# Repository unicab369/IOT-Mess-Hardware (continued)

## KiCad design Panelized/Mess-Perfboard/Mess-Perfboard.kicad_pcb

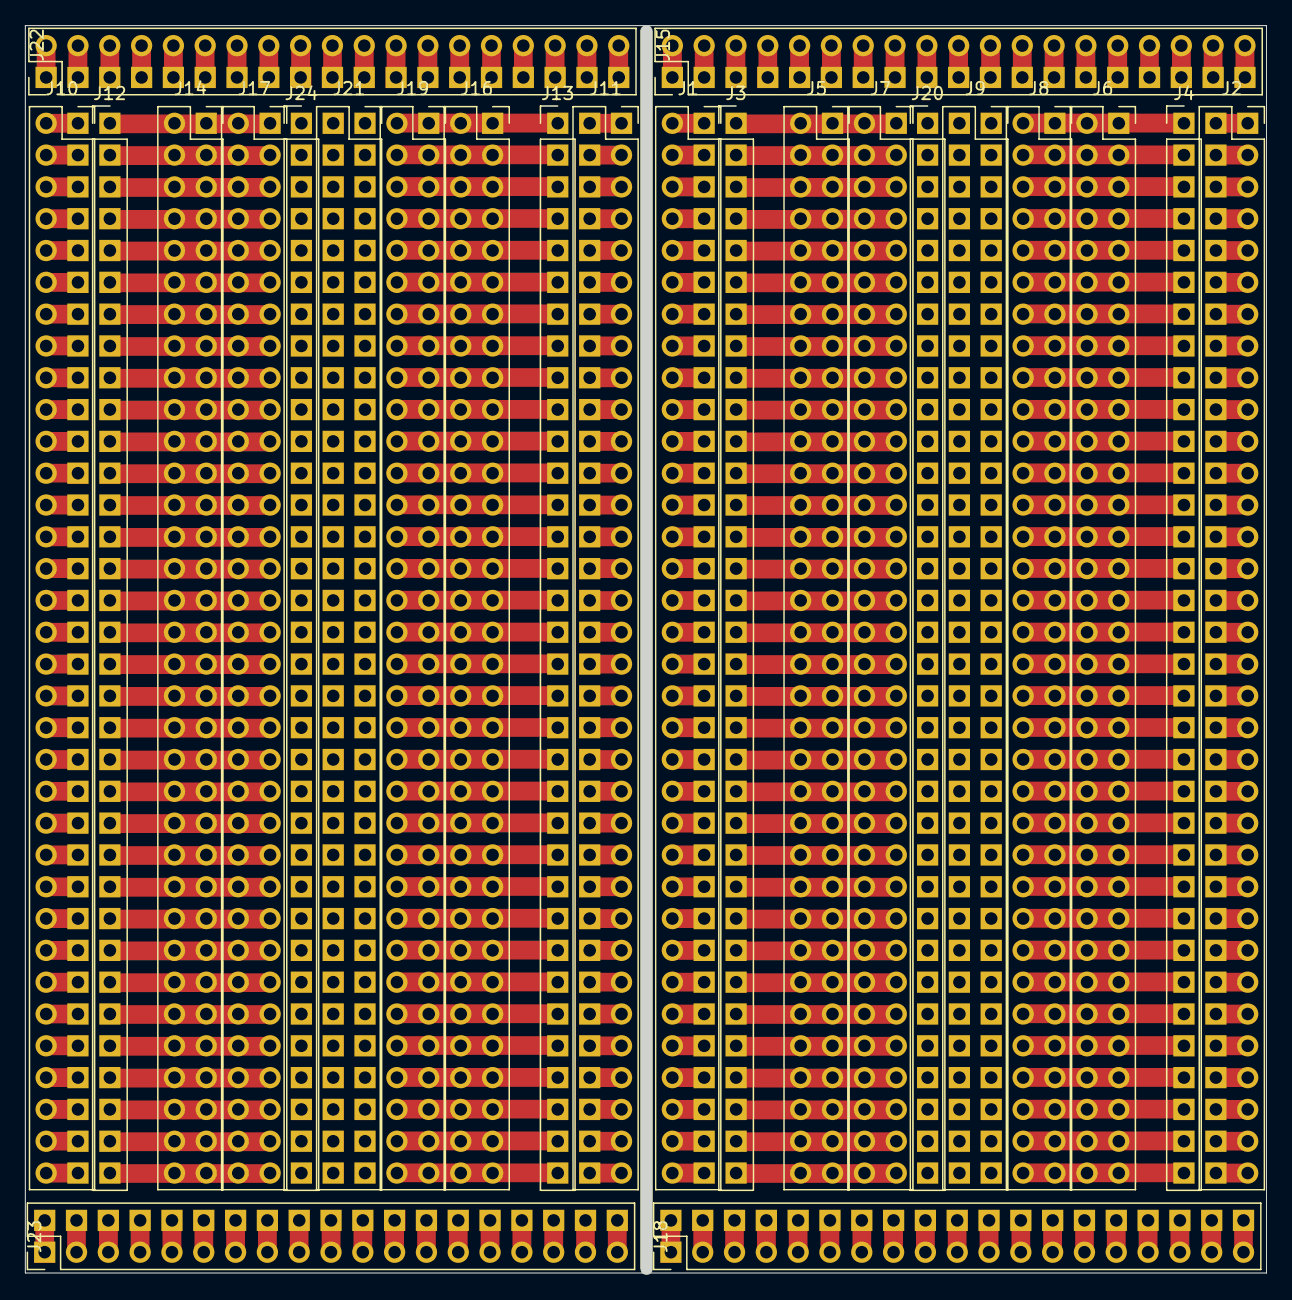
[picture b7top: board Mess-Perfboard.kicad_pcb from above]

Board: 2 copper layers, 99.1 x 99.6 mm, 24 parts (0 on the bottom side), 174 nets.

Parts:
J1, J2, J5, J6, J7, J8, J9, J10, J11, J14, J16, J17, J19, J21: Conn_02x34_Odd_Even; PinSocket_2x34_P2.54mm_Vertical
J3, J4, J12, J13, J20, J24: Conn_01x34_Pin; PinHeader_1x34_P2.54mm_Vertical
J15, J18, J22, J23: Conn_02x19_Odd_Even; PinHeader_2x19_P2.54mm_Vertical

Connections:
/A1: J1.1, J1.2, J10.1, J10.2
/A2: J1.3, J1.4, J10.3, J10.4
/A3: J1.5, J1.6, J10.5, J10.6
/A4: J1.7, J1.8, J10.7, J10.8
/A5: J1.9, J1.10, J10.9, J10.10
/A6: J1.11, J1.12, J10.11, J10.12
/A7: J1.13, J1.14, J10.13, J10.14
/A8: J1.15, J1.16, J10.15, J10.16
/A9: J1.17, J1.18, J10.17, J10.18
/A10: J1.19, J1.20, J10.19, J10.20
/A11: J1.21, J1.22, J10.21, J10.22
/A12: J1.23, J1.24, J10.23, J10.24
/A13: J1.25, J1.26, J10.25, J10.26
/A14: J1.27, J1.28, J10.27, J10.28
/A15: J1.29, J1.30, J10.29, J10.30
/A16: J1.31, J1.32, J10.31, J10.32
/A17: J1.33, J1.34, J10.33, J10.34
/A18: J1.35, J1.36, J10.35, J10.36
/A19: J1.37, J1.38, J10.37, J10.38
/A20: J1.39, J1.40, J10.39, J10.40
/A21: J1.41, J1.42, J10.41, J10.42
/A22: J1.43, J1.44, J10.43, J10.44
/A23: J1.45, J1.46, J10.45, J10.46
/A24: J1.47, J1.48, J10.47, J10.48
/A25: J1.49, J1.50, J10.49, J10.50
/A26: J1.51, J1.52, J10.51, J10.52
/A27: J1.53, J1.54, J10.53, J10.54
/A28: J1.55, J1.56, J10.55, J10.56
/A29: J1.57, J1.58, J10.57, J10.58
/A30: J1.59, J1.60, J10.59, J10.60
/A31: J1.61, J1.62, J10.61, J10.62
/A32: J1.63, J1.64, J10.63, J10.64
/A33: J1.65, J1.66, J10.65, J10.66
/A34: J1.67, J1.68, J10.67, J10.68
/B1: J3.1, J5.1, J5.2, J7.1, J7.2, J12.1, J14.1, J14.2, J17.1, J17.2
/B2: J3.2, J5.3, J5.4, J7.3, J7.4, J12.2, J14.3, J14.4, J17.3, J17.4
/B3: J3.3, J5.5, J5.6, J7.5, J7.6, J12.3, J14.5, J14.6, J17.5, J17.6
/B4: J3.4, J5.7, J5.8, J7.7, J7.8, J12.4, J14.7, J14.8, J17.7, J17.8
/B5: J3.5, J5.9, J5.10, J7.9, J7.10, J12.5, J14.9, J14.10, J17.9, J17.10
/B6: J3.6, J5.11, J5.12, J7.11, J7.12, J12.6, J14.11, J14.12, J17.11, J17.12
/B7: J3.7, J5.13, J5.14, J7.13, J7.14, J12.7, J14.13, J14.14, J17.13, J17.14
/B8: J3.8, J5.15, J5.16, J7.15, J7.16, J12.8, J14.15, J14.16, J17.15, J17.16
/B9: J3.9, J5.17, J5.18, J7.17, J7.18, J12.9, J14.17, J14.18, J17.17, J17.18
/B10: J3.10, J5.19, J5.20, J7.19, J7.20, J12.10, J14.19, J14.20, J17.19, J17.20
/B11: J3.11, J5.21, J5.22, J7.21, J7.22, J12.11, J14.21, J14.22, J17.21, J17.22
/B12: J3.12, J5.23, J5.24, J7.23, J7.24, J12.12, J14.23, J14.24, J17.23, J17.24
/B13: J3.13, J5.25, J5.26, J7.25, J7.26, J12.13, J14.25, J14.26, J17.25, J17.26
/B14: J3.14, J5.27, J5.28, J7.27, J7.28, J12.14, J14.27, J14.28, J17.27, J17.28
/B15: J3.15, J5.29, J5.30, J7.29, J7.30, J12.15, J14.29, J14.30, J17.29, J17.30
/B16: J3.16, J5.31, J5.32, J7.31, J7.32, J12.16, J14.31, J14.32, J17.31, J17.32
/B17: J3.17, J5.33, J5.34, J7.33, J7.34, J12.17, J14.33, J14.34, J17.33, J17.34
/B18: J3.18, J5.35, J5.36, J7.35, J7.36, J12.18, J14.35, J14.36, J17.35, J17.36
/B19: J3.19, J5.37, J5.38, J7.37, J7.38, J12.19, J14.37, J14.38, J17.37, J17.38
/B20: J3.20, J5.39, J5.40, J7.39, J7.40, J12.20, J14.39, J14.40, J17.39, J17.40
/B21: J3.21, J5.41, J5.42, J7.41, J7.42, J12.21, J14.41, J14.42, J17.41, J17.42
/B22: J3.22, J5.43, J5.44, J7.43, J7.44, J12.22, J14.43, J14.44, J17.43, J17.44
/B23: J3.23, J5.45, J5.46, J7.45, J7.46, J12.23, J14.45, J14.46, J17.45, J17.46
/B24: J3.24, J5.47, J5.48, J7.47, J7.48, J12.24, J14.47, J14.48, J17.47, J17.48
/B25: J3.25, J5.49, J5.50, J7.49, J7.50, J12.25, J14.49, J14.50, J17.49, J17.50
/B26: J3.26, J5.51, J5.52, J7.51, J7.52, J12.26, J14.51, J14.52, J17.51, J17.52
/B27: J3.27, J5.53, J5.54, J7.53, J7.54, J12.27, J14.53, J14.54, J17.53, J17.54
/B28: J3.28, J5.55, J5.56, J7.55, J7.56, J12.28, J14.55, J14.56, J17.55, J17.56
/B29: J3.29, J5.57, J5.58, J7.57, J7.58, J12.29, J14.57, J14.58, J17.57, J17.58
/B30: J3.30, J5.59, J5.60, J7.59, J7.60, J12.30, J14.59, J14.60, J17.59, J17.60
/B31: J3.31, J5.61, J5.62, J7.61, J7.62, J12.31, J14.61, J14.62, J17.61, J17.62
/B32: J3.32, J5.63, J5.64, J7.63, J7.64, J12.32, J14.63, J14.64, J17.63, J17.64
/B33: J3.33, J5.65, J5.66, J7.65, J7.66, J12.33, J14.65, J14.66, J17.65, J17.66
/B34: J3.34, J5.67, J5.68, J7.67, J7.68, J12.34, J14.67, J14.68, J17.67, J17.68
/C1: J2.1, J2.2, J11.1, J11.2
/C2: J2.3, J2.4, J11.3, J11.4
/C3: J2.5, J2.6, J11.5, J11.6
/C4: J2.7, J2.8, J11.7, J11.8
/C5: J2.9, J2.10, J11.9, J11.10
/C6: J2.11, J2.12, J11.11, J11.12
/C7: J2.13, J2.14, J11.13, J11.14
/C8: J2.15, J2.16, J11.15, J11.16
/C9: J2.17, J2.18, J11.17, J11.18
/C10: J2.19, J2.20, J11.19, J11.20
/C11: J2.21, J2.22, J11.21, J11.22
/C12: J2.23, J2.24, J11.23, J11.24
/C13: J2.25, J2.26, J11.25, J11.26
/C14: J2.27, J2.28, J11.27, J11.28
/C15: J2.29, J2.30, J11.29, J11.30
/C16: J2.31, J2.32, J11.31, J11.32
/C17: J2.33, J2.34, J11.33, J11.34
/C18: J2.35, J2.36, J11.35, J11.36
/C19: J2.37, J2.38, J11.37, J11.38
/C20: J2.39, J2.40, J11.39, J11.40
/C21: J2.41, J2.42, J11.41, J11.42
/C22: J2.43, J2.44, J11.43, J11.44
/C23: J2.45, J2.46, J11.45, J11.46
/C24: J2.47, J2.48, J11.47, J11.48
/C25: J2.49, J2.50, J11.49, J11.50
/C26: J2.51, J2.52, J11.51, J11.52
/C27: J2.53, J2.54, J11.53, J11.54
/C28: J2.55, J2.56, J11.55, J11.56
/C29: J2.57, J2.58, J11.57, J11.58
/C30: J2.59, J2.60, J11.59, J11.60
/C31: J2.61, J2.62, J11.61, J11.62
/C32: J2.63, J2.64, J11.63, J11.64
/C33: J2.65, J2.66, J11.65, J11.66
/C34: J2.67, J2.68, J11.67, J11.68
/D1: J4.1, J6.1, J6.2, J8.1, J8.2, J13.1, J16.1, J16.2, J19.1, J19.2
/D2: J4.2, J6.3, J6.4, J8.3, J8.4, J13.2, J16.3, J16.4, J19.3, J19.4
/D3: J4.3, J6.5, J6.6, J8.5, J8.6, J13.3, J16.5, J16.6, J19.5, J19.6
/D4: J4.4, J6.7, J6.8, J8.7, J8.8, J13.4, J16.7, J16.8, J19.7, J19.8
/D5: J4.5, J6.9, J6.10, J8.9, J8.10, J13.5, J16.9, J16.10, J19.9, J19.10
/D6: J4.6, J6.11, J6.12, J8.11, J8.12, J13.6, J16.11, J16.12, J19.11, J19.12
/D7: J4.7, J6.13, J6.14, J8.13, J8.14, J13.7, J16.13, J16.14, J19.13, J19.14
/D8: J4.8, J6.15, J6.16, J8.15, J8.16, J13.8, J16.15, J16.16, J19.15, J19.16
/D9: J4.9, J6.17, J6.18, J8.17, J8.18, J13.9, J16.17, J16.18, J19.17, J19.18
/D10: J4.10, J6.19, J6.20, J8.19, J8.20, J13.10, J16.19, J16.20, J19.19, J19.20
/D11: J4.11, J6.21, J6.22, J8.21, J8.22, J13.11, J16.21, J16.22, J19.21, J19.22
/D12: J4.12, J6.23, J6.24, J8.23, J8.24, J13.12, J16.23, J16.24, J19.23, J19.24
/D13: J4.13, J6.25, J6.26, J8.25, J8.26, J13.13, J16.25, J16.26, J19.25, J19.26
/D14: J4.14, J6.27, J6.28, J8.27, J8.28, J13.14, J16.27, J16.28, J19.27, J19.28
/D15: J4.15, J6.29, J6.30, J8.29, J8.30, J13.15, J16.29, J16.30, J19.29, J19.30
/D16: J4.16, J6.31, J6.32, J8.31, J8.32, J13.16, J16.31, J16.32, J19.31, J19.32
/D17: J4.17, J6.33, J6.34, J8.33, J8.34, J13.17, J16.33, J16.34, J19.33, J19.34
/D18: J4.18, J6.35, J6.36, J8.35, J8.36, J13.18, J16.35, J16.36, J19.35, J19.36
/D19: J4.19, J6.37, J6.38, J8.37, J8.38, J13.19, J16.37, J16.38, J19.37, J19.38
/D20: J4.20, J6.39, J6.40, J8.39, J8.40, J13.20, J16.39, J16.40, J19.39, J19.40
/D21: J4.21, J6.41, J6.42, J8.41, J8.42, J13.21, J16.41, J16.42, J19.41, J19.42
/D22: J4.22, J6.43, J6.44, J8.43, J8.44, J13.22, J16.43, J16.44, J19.43, J19.44
/D23: J4.23, J6.45, J6.46, J8.45, J8.46, J13.23, J16.45, J16.46, J19.45, J19.46
/D24: J4.24, J6.47, J6.48, J8.47, J8.48, J13.24, J16.47, J16.48, J19.47, J19.48
/D25: J4.25, J6.49, J6.50, J8.49, J8.50, J13.25, J16.49, J16.50, J19.49, J19.50
/D26: J4.26, J6.51, J6.52, J8.51, J8.52, J13.26, J16.51, J16.52, J19.51, J19.52
/D27: J4.27, J6.53, J6.54, J8.53, J8.54, J13.27, J16.53, J16.54, J19.53, J19.54
/D28: J4.28, J6.55, J6.56, J8.55, J8.56, J13.28, J16.55, J16.56, J19.55, J19.56
/D29: J4.29, J6.57, J6.58, J8.57, J8.58, J13.29, J16.57, J16.58, J19.57, J19.58
/D30: J4.30, J6.59, J6.60, J8.59, J8.60, J13.30, J16.59, J16.60, J19.59, J19.60
/D31: J4.31, J6.61, J6.62, J8.61, J8.62, J13.31, J16.61, J16.62, J19.61, J19.62
/D32: J4.32, J6.63, J6.64, J8.63, J8.64, J13.32, J16.63, J16.64, J19.63, J19.64
/D33: J4.33, J6.65, J6.66, J8.65, J8.66, J13.33, J16.65, J16.66, J19.65, J19.66
/D34: J4.34, J6.67, J6.68, J8.67, J8.68, J13.34, J16.67, J16.68, J19.67, J19.68
/E1: J15.1, J15.2, J22.1, J22.2
/E2: J15.3, J15.4, J22.3, J22.4
/E3: J15.5, J15.6, J22.5, J22.6
/E4: J15.7, J15.8, J22.7, J22.8
/E5: J15.9, J15.10, J22.9, J22.10
/E6: J15.11, J15.12, J22.11, J22.12
/E7: J15.13, J15.14, J22.13, J22.14
/E8: J15.15, J15.16, J22.15, J22.16
/E9: J15.17, J15.18, J22.17, J22.18
/E10: J15.19, J15.20, J22.19, J22.20
/E11: J15.21, J15.22, J22.21, J22.22
/E12: J15.23, J15.24, J22.23, J22.24
/E13: J15.25, J15.26, J22.25, J22.26
/E14: J15.27, J15.28, J22.27, J22.28
/E15: J15.29, J15.30, J22.29, J22.30
/E16: J15.31, J15.32, J22.31, J22.32
/E17: J15.33, J15.34, J22.33, J22.34
/E18: J15.35, J15.36, J22.35, J22.36
/E19: J15.37, J15.38, J22.37, J22.38
/F1: J18.1, J18.2, J23.1, J23.2
/F2: J18.3, J18.4, J23.3, J23.4
/F3: J18.5, J18.6, J23.5, J23.6
/F4: J18.7, J18.8, J23.7, J23.8
/F5: J18.9, J18.10, J23.9, J23.10
/F6: J18.11, J18.12, J23.11, J23.12
/F7: J18.13, J18.14, J23.13, J23.14
/F8: J18.15, J18.16, J23.15, J23.16
/F9: J18.17, J18.18, J23.17, J23.18
/F10: J18.19, J18.20, J23.19, J23.20
/F11: J18.21, J18.22, J23.21, J23.22
/F12: J18.23, J18.24, J23.23, J23.24
/F13: J18.25, J18.26, J23.25, J23.26
/F14: J18.27, J18.28, J23.27, J23.28
/F15: J18.29, J18.30, J23.29, J23.30
/F16: J18.31, J18.32, J23.31, J23.32
/F17: J18.33, J18.34, J23.33, J23.34
/F18: J18.35, J18.36, J23.35, J23.36
/F19: J18.37, J18.38, J23.37, J23.38

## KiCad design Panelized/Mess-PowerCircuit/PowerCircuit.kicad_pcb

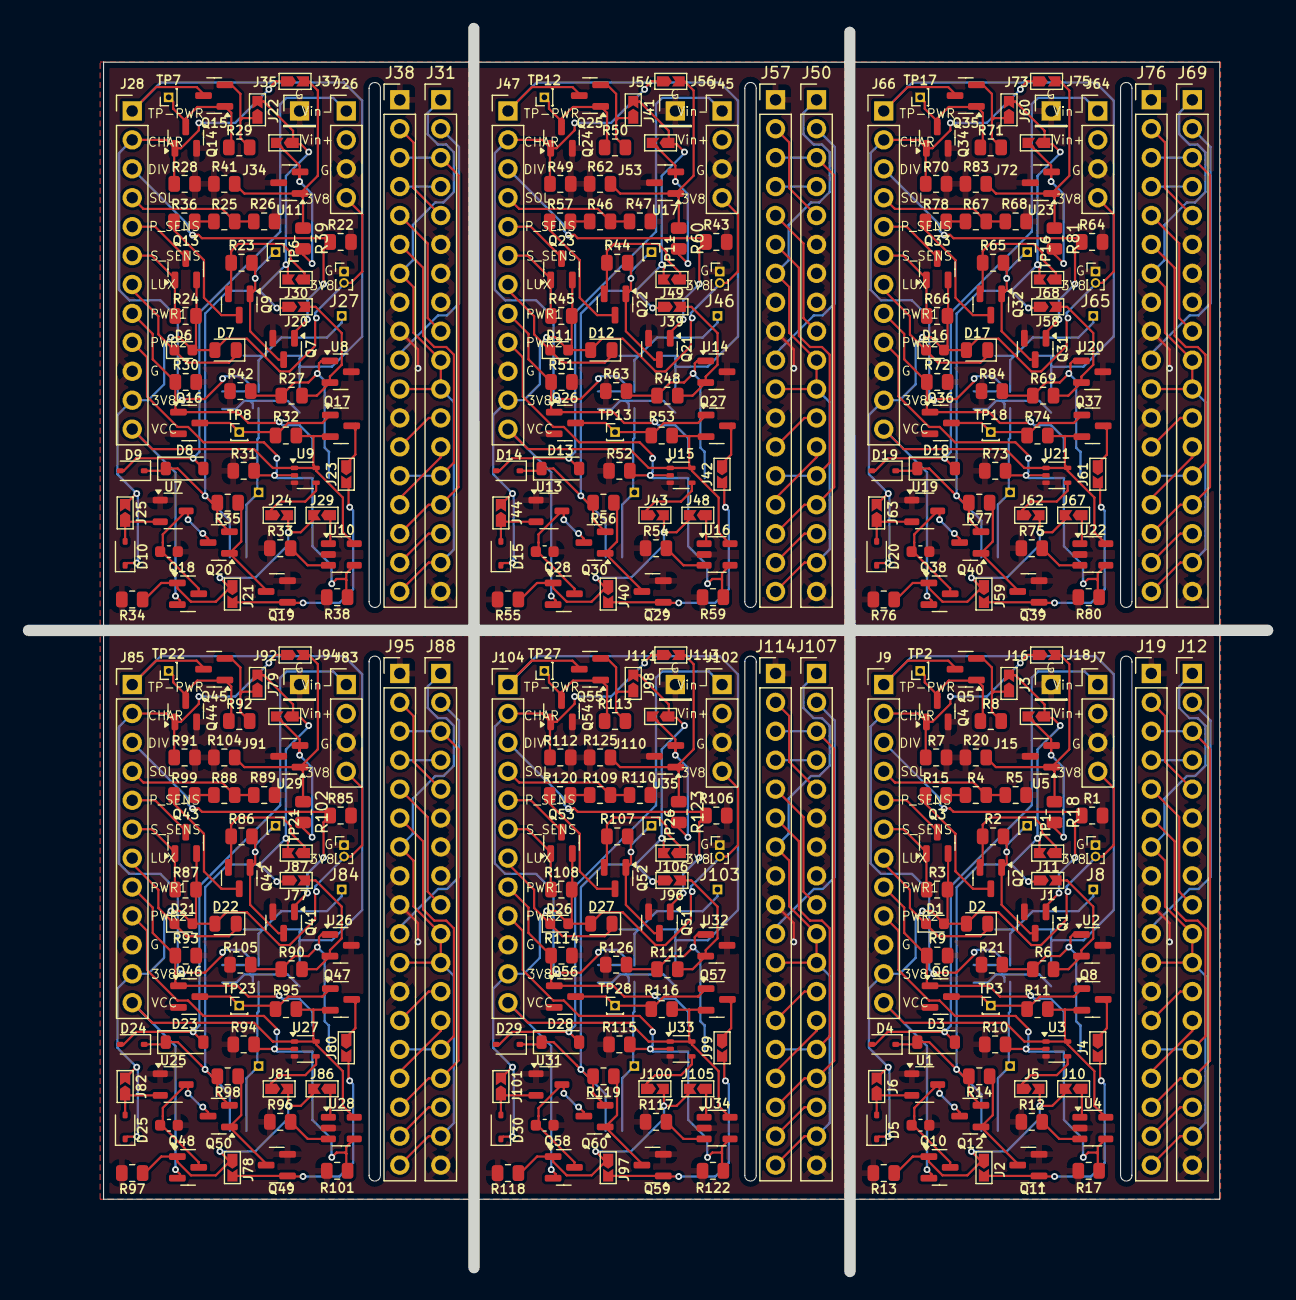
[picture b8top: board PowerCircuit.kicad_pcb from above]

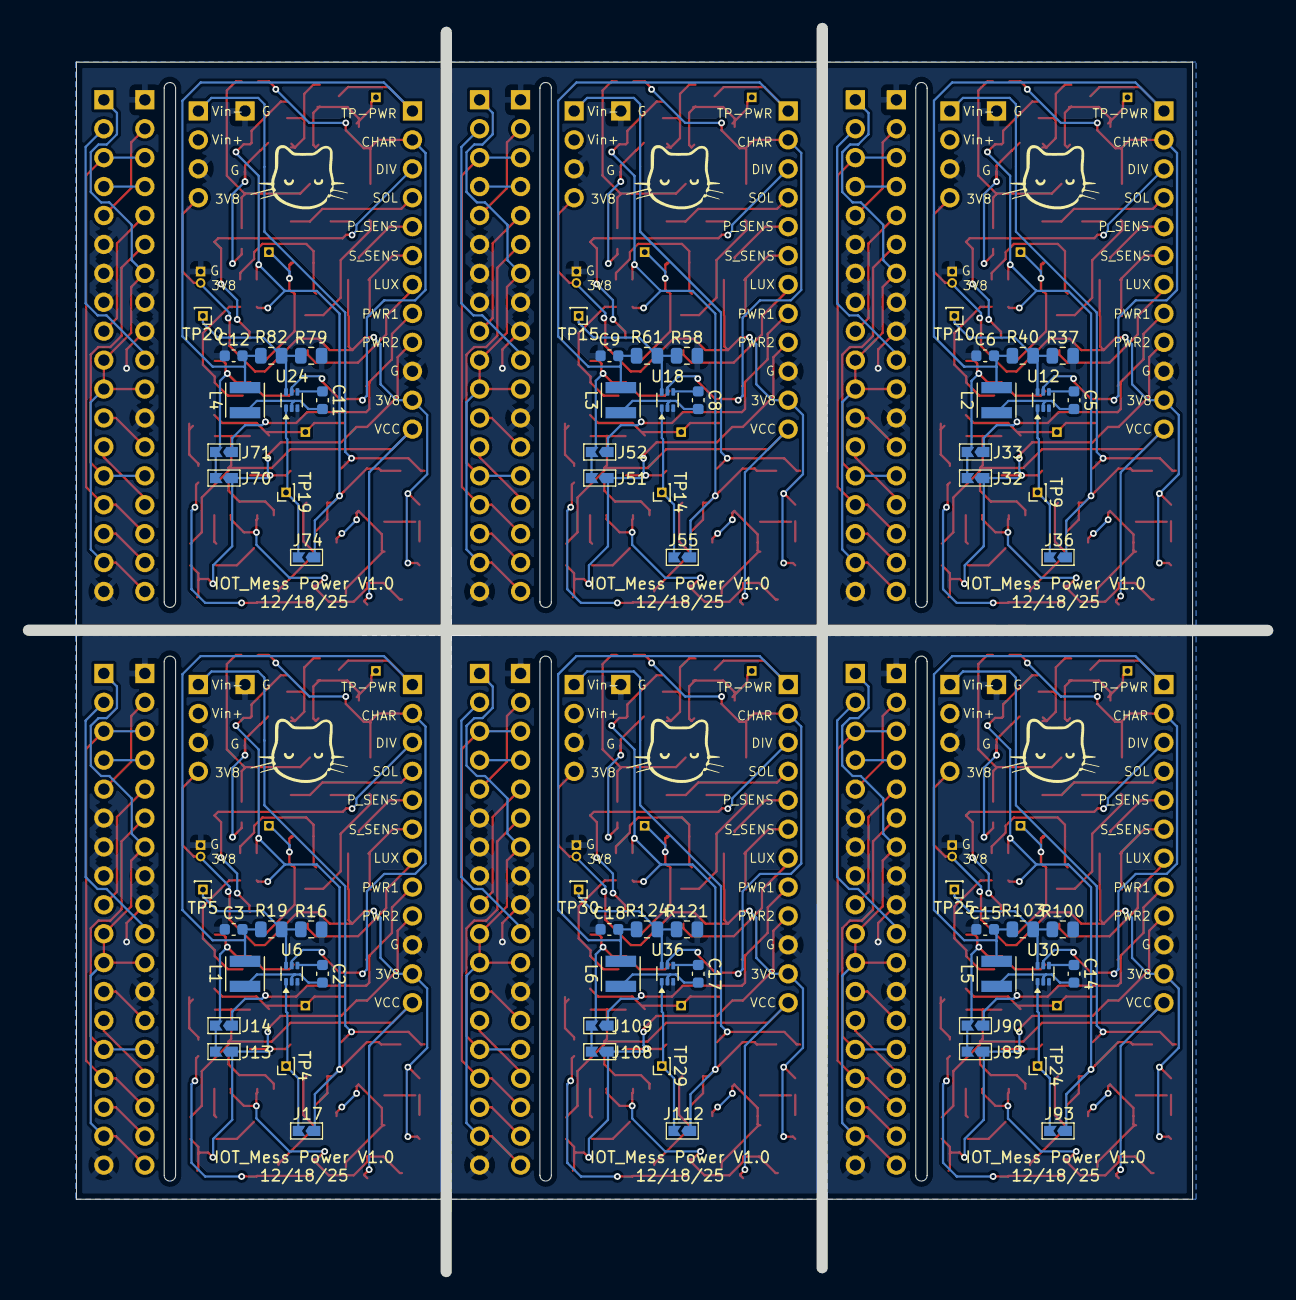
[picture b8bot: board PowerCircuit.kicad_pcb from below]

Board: 2 copper layers, 98.0 x 99.9 mm, 420 parts (66 on the bottom side), 49 nets.

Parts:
C1, C2, C3, C4, C5, C6, C7, C8, C9, C10, C11, C12, C13, C14, C15, C16, C17, C18: C; C_0603_1608Metric
D1, D6, D11, D16, D21, D26: D_Photo; LED_0603_1608Metric
D2, D7, D12, D17, D22, D27: D_Photo; LED_0805_2012Metric
D3, D8, D13, D18, D23, D28: MBR0520; D_SOD-123
D4, D5, D9, D10, D14, D15, D19, D20, D24, D25, D29, D30: BAT48JFILM; D_SOD-323
J1, J2, J3, J4, J5, J6, J10, J11, J13, J14, J15, J16, J17, J20, J21, J22, J23, J24, J25, J29, J30, J32, J33, J34, J35, J36, J39, J40, J41, J42, J43, J44, J48, J49, J51, J52, J53, J54, J55, J58, J59, J60, J61, J62, J63, J67, J68, J70, J71, J72, J73, J74, J77, J78, J79, J80, J81, J82, J86, J87, J89, J90, J91, J92, J93, J96, J97, J98, J99, J100, J101, J105, J106, J108, J109, J110, J111, J112: Jumper_2; Jumpper-triangle
J7, J26, J45, J64, J83, J102: Conn_01x04_Pin; PinHeader_1x04_P2.54mm_Vertical
J8, J27, J46, J65, J84, J103: Conn_01x02_Pin; PinHeader_1x02_P1.00mm_Vertical
J9, J28, J47, J66, J85, J104: Conn_01x12_Pin; PinHeader_1x12_P2.54mm_Vertical
J12, J19, J31, J38, J50, J57, J69, J76, J88, J95, J107, J114: Conn_01x18_Pin; PinHeader_1x18_P2.54mm_Vertical
J18, J37, J56, J75, J94, J113: Conn_01x01_Pin; PinHeader_1x01_P2.54mm_Vertical
L1, L2, L3, L4, L5, L6: L; L_Neosid_SMS-ME3010
Q1, Q4, Q6, Q7, Q11, Q14, Q16, Q19, Q21, Q24, Q26, Q29, Q31, Q34, Q36, Q39, Q41, Q44, Q46, Q49, Q51, Q54, Q56, Q59: AO3400A; SOT-23
Q2, Q3, Q5, Q8, Q9, Q10, Q12, Q13, Q15, Q17, Q18, Q20, Q22, Q23, Q25, Q27, Q28, Q30, Q32, Q33, Q35, Q37, Q38, Q40, Q42, Q43, Q45, Q47, Q48, Q50, Q52, Q53, Q55, Q57, Q58, Q60: AO3401A (P-Fet); SOT-23
R1, R3, R7, R9, R10, R11, R13, R14, R22, R24, R28, R30, R31, R32, R34, R35, R43, R45, R49, R51, R52, R53, R55, R56, R64, R66, R70, R72, R73, R74, R76, R77, R85, R87, R91, R93, R94, R95, R97, R98, R106, R108, R112, R114, R115, R116, R118, R119: 100K; R_0805_2012Metric
R2, R4, R5, R6, R8, R12, R15, R16, R17, R18, R19, R20, R21, R23, R25, R26, R27, R29, R33, R36, R37, R38, R39, R40, R41, R42, R44, R46, R47, R48, R50, R54, R57, R58, R59, R60, R61, R62, R63, R65, R67, R68, R69, R71, R75, R78, R79, R80, R81, R82, R83, R84, R86, R88, R89, R90, R92, R96, R99, R100, R101, R102, R103, R104, R105, R107, R109, R110, R111, R113, R117, R120, R121, R122, R123, R124, R125, R126: 10K; R_0805_2012Metric
TP1, TP2, TP3, TP4, TP5, TP6, TP7, TP8, TP9, TP10, TP11, TP12, TP13, TP14, TP15, TP16, TP17, TP18, TP19, TP20, TP21, TP22, TP23, TP24, TP25, TP26, TP27, TP28, TP29, TP30: TestPoint; PinHeader_1x01_P1.00mm_Vertical
U1, U7, U13, U19, U25, U31: XC6206PxxxMR; SOT-23-3
U2, U5, U8, U11, U14, U17, U20, U23, U26, U29, U32, U35: LT431 (Voltage Ref); SOT-23
U3, U9, U15, U21, U27, U33: 74LV1T08GW; SOT-353_SC-70-5
U4, U10, U16, U22, U28, U34: MT9700; SOT-23-5
U6, U12, U18, U24, U30, U36: TPS562202; SOT-563

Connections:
+3V3: J12.1, J12.10, J12.11, J12.17, J19.7, J19.11, J19.18, J31.1, J31.10, J31.11, J31.17, J38.7, J38.11, J38.18, J50.1, J50.10, J50.11, J50.17, J57.7, J57.11, J57.18, J69.1, J69.10, J69.11, J69.17, J76.7, J76.11, J76.18, J88.1, J88.10, J88.11, J88.17, J95.7, J95.11, J95.18, J107.1, J107.10, J107.11, J107.17, J114.7, J114.11, J114.18
+3V8: D1.2 (A), D2.2 (A), D5.1 (K), D6.2 (A), D7.2 (A), D10.1 (K), D11.2 (A), D12.2 (A), D15.1 (K), D16.2 (A), D17.2 (A), D20.1 (K), D21.2 (A), D22.2 (A), D25.1 (K), D26.2 (A), D27.2 (A), D30.1 (K), J6.2 (B), J7.4, J8.2, J9.11, J25.2 (B), J26.4, J27.2, J28.11, J44.2 (B), J45.4, J46.2, J47.11, J63.2 (B), J64.4, J65.2, J66.11, J82.2 (B), J83.4, J84.2, J85.11, J101.2 (B), J102.4, J103.2, J104.11, Q3.2 (S), Q13.2 (S), Q23.2 (S), Q33.2 (S), Q43.2 (S), Q53.2 (S), R3.2, R24.2, R45.2, R66.2, R87.2, R108.2
ADC_LUX: D1.1 (K), D2.1 (K), D6.1 (K), D7.1 (K), D11.1 (K), D12.1 (K), D16.1 (K), D17.1 (K), D21.1 (K), D22.1 (K), D26.1 (K), D27.1 (K), J9.7, J28.7, J47.7, J66.7, J85.7, J104.7
ADC_SOLAR: J9.4, J28.4, J47.4, J66.4, J85.4, J104.4, R4.1, R5.2, R25.1, R26.2, R46.1, R47.2, R67.1, R68.2, R88.1, R89.2, R109.1, R110.2
CLK: J12.4, J19.4, J31.4, J38.4, J50.4, J57.4, J69.4, J76.4, J88.4, J95.4, J107.4, J114.4
CS_0: J12.12, J19.13, J31.12, J38.13, J50.12, J57.13, J69.12, J76.13, J88.12, J95.13, J107.12, J114.13
CS_1: J12.2, J19.10, J31.2, J38.10, J50.2, J57.10, J69.2, J76.10, J88.2, J95.10, J107.2, J114.10
CS_2: J12.9, J19.5, J31.9, J38.5, J50.9, J57.5, J69.9, J76.5, J88.9, J95.5, J107.9, J114.5
DC: J12.13, J19.15, J31.13, J38.15, J50.13, J57.15, J69.13, J76.15, J88.13, J95.15, J107.13, J114.15
GND: C1.2, C3.1, C4.2, C6.1, C7.2, C9.1, C10.2, C12.1, C13.2, C15.1, C16.2, C18.1, J7.3, J8.1, J9.10, J12.6, J12.7, J12.8, J12.18, J18.1, J19.1, J19.8, J19.9, J19.12, J26.3, J27.1, J28.10, J31.6, J31.7, J31.8, J31.18, J37.1, J38.1, J38.8, J38.9, J38.12, J45.3, J46.1, J47.10, J50.6, J50.7, J50.8, J50.18, J56.1, J57.1, J57.8, J57.9, J57.12, J64.3, J65.1, J66.10, J69.6, J69.7, J69.8, J69.18, J75.1, J76.1, J76.8, J76.9, J76.12, J83.3, J84.1, J85.10, J88.6, J88.7, J88.8, J88.18, J94.1, J95.1, J95.8, J95.9, J95.12, J102.3, J103.1, J104.10, J107.6, J107.7, J107.8, J107.18, J113.1, J114.1, J114.8, J114.9, J114.12, Q1.2 (S), Q4.2 (S), Q6.2 (S), Q7.2 (S), Q11.2 (S), Q14.2 (S), Q16.2 (S), Q19.2 (S), Q21.2 (S), Q24.2 (S), Q26.2 (S), Q29.2 (S), Q31.2 (S), Q34.2 (S), Q36.2 (S), Q39.2 (S), Q41.2 (S), Q44.2 (S), Q46.2 (S), Q49.2 (S), Q51.2 (S), Q54.2 (S), Q56.2 (S), Q59.2 (S), R1.1, R5.1, R7.1, R9.1, R10.1, R12.1, R13.1, R16.1, R17.1, R20.1, R21.1, R22.1, R26.1, R28.1, R30.1, R31.1, R33.1, R34.1, R37.1, R38.1, R41.1, R42.1, R43.1, R47.1, R49.1, R51.1, R52.1, R54.1, R55.1, R58.1, R59.1, R62.1, R63.1, R64.1, R68.1, R70.1, R72.1, R73.1, R75.1, R76.1, R79.1, R80.1, R83.1, R84.1, R85.1, R89.1, R91.1, R93.1, R94.1, R96.1, R97.1, R100.1, R101.1, R104.1, R105.1, R106.1, R110.1, R112.1, R114.1, R115.1, R117.1, R118.1, R121.1, R122.1, R125.1, R126.1, U1.1 (GND), U2.3 (GND), U3.3 (GND), U4.2 (GND), U5.3 (GND), U6.3 (GND), U7.1 (GND), U8.3 (GND), U9.3 (GND), U10.2 (GND), U11.3 (GND), U12.3 (GND), U13.1 (GND), U14.3 (GND), U15.3 (GND), U16.2 (GND), U17.3 (GND), U18.3 (GND), U19.1 (GND), U20.3 (GND), U21.3 (GND), U22.2 (GND), U23.3 (GND), U24.3 (GND), U25.1 (GND), U26.3 (GND), U27.3 (GND), U28.2 (GND), U29.3 (GND), U30.3 (GND), U31.1 (GND), U32.3 (GND), U33.3 (GND), U34.2 (GND), U35.3 (GND), U36.3 (GND)
IN-: D3.2 (A), D4.2 (A), D8.2 (A), D9.2 (A), D13.2 (A), D14.2 (A), D18.2 (A), D19.2 (A), D23.2 (A), D24.2 (A), D28.2 (A), D29.2 (A), J7.1, J26.1, J45.1, J64.1, J83.1, J102.1
MISO: J12.5, J19.2, J31.5, J38.2, J50.5, J57.2, J69.5, J76.2, J88.5, J95.2, J107.5, J114.2
MOSI: J12.3, J12.15, J19.3, J19.16, J31.3, J31.15, J38.3, J38.16, J50.3, J50.15, J57.3, J57.16, J69.3, J69.15, J76.3, J76.16, J88.3, J88.15, J95.3, J95.16, J107.3, J107.15, J114.3, J114.16
unnamed: D3.1 (K), D4.1 (K), D8.1 (K), D9.1 (K), D13.1 (K), D14.1 (K), D18.1 (K), D19.1 (K), D23.1 (K), D24.1 (K), D28.1 (K), D29.1 (K), J1.2 (B), J3.2 (B), J11.1 (A), J15.1 (A), J17.1 (A), J20.2 (B), J22.2 (B), J30.1 (A), J34.1 (A), J36.1 (A), J39.2 (B), J41.2 (B), J49.1 (A), J53.1 (A), J55.1 (A), J58.2 (B), J60.2 (B), J68.1 (A), J72.1 (A), J74.1 (A), J77.2 (B), J79.2 (B), J87.1 (A), J91.1 (A), J93.1 (A), J96.2 (B), J98.2 (B), J106.1 (A), J110.1 (A), J112.1 (A), Q12.2 (S), Q20.2 (S), Q30.2 (S), Q40.2 (S), Q50.2 (S), Q60.2 (S), R14.2, R35.2, R56.2, R77.2, R98.2, R119.2
unnamed: D5.2 (A), D10.2 (A), D15.2 (A), D20.2 (A), D25.2 (A), D30.2 (A), J6.1 (A), J25.1 (A), J44.1 (A), J63.1 (A), J82.1 (A), J101.1 (A), U1.2 (VO), U7.2 (VO), U13.2 (VO), U19.2 (VO), U25.2 (VO), U31.2 (VO)
unnamed: J1.1 (A), J20.1 (A), J39.1 (A), J58.1 (A), J77.1 (A), J96.1 (A), Q2.2 (S), Q9.2 (S), Q22.2 (S), Q32.2 (S), Q42.2 (S), Q52.2 (S), R2.2, R23.2, R44.2, R65.2, R86.2, R107.2
unnamed: J2.2 (B), J4.2 (B), J21.2 (B), J23.2 (B), J40.2 (B), J42.2 (B), J59.2 (B), J61.2 (B), J78.2 (B), J80.2 (B), J97.2 (B), J99.2 (B), Q11.1 (G), Q19.1 (G), Q29.1 (G), Q39.1 (G), Q49.1 (G), Q59.1 (G)
unnamed: J3.1 (A), J22.1 (A), J41.1 (A), J60.1 (A), J79.1 (A), J98.1 (A), Q5.2 (S), Q15.2 (S), Q25.2 (S), Q35.2 (S), Q45.2 (S), Q55.2 (S), R8.2, R29.2, R50.2, R71.2, R92.2, R113.2
unnamed: J4.1 (A), J23.1 (A), J42.1 (A), J61.1 (A), J80.1 (A), J99.1 (A), Q8.3 (D), Q17.3 (D), Q27.3 (D), Q37.3 (D), Q47.3 (D), Q57.3 (D)
unnamed: J5.1 (A), J24.1 (A), J43.1 (A), J62.1 (A), J81.1 (A), J100.1 (A), U3.4 (Y), U9.4 (Y), U15.4 (Y), U21.4 (Y), U27.4 (Y), U33.4 (Y)
unnamed: J10.1 (A), J29.1 (A), J48.1 (A), J67.1 (A), J86.1 (A), J105.1 (A), U4.1 (OUT), U10.1 (OUT), U16.1 (OUT), U22.1 (OUT), U28.1 (OUT), U34.1 (OUT)
unnamed: J2.1 (A), J5.2 (B), J10.2 (B), J21.1 (A), J24.2 (B), J29.2 (B), J40.1 (A), J43.2 (B), J48.2 (B), J59.1 (A), J62.2 (B), J67.2 (B), J78.1 (A), J81.2 (B), J86.2 (B), J97.1 (A), J100.2 (B), J105.2 (B), Q10.1 (G), Q18.1 (G), Q28.1 (G), Q38.1 (G), Q48.1 (G), Q58.1 (G), R13.2, R34.2, R55.2, R76.2, R97.2, R118.2
unnamed: J11.2 (B), J30.2 (B), J49.2 (B), J68.2 (B), J87.2 (B), J106.2 (B), R6.2, R27.2, R48.2, R69.2, R90.2, R111.2, U2.2 (VDD), U8.2 (VDD), U14.2 (VDD), U20.2 (VDD), U26.2 (VDD), U32.2 (VDD)
unnamed: J13.2 (B), J14.2 (B), J32.2 (B), J33.2 (B), J51.2 (B), J52.2 (B), J70.2 (B), J71.2 (B), J89.2 (B), J90.2 (B), J108.2 (B), J109.2 (B), R6.1, R21.2, R27.1, R42.2, R48.1, R63.2, R69.1, R84.2, R90.1, R105.2, R111.1, R126.2, U2.1 (VOUT), U8.1 (VOUT), U14.1 (VOUT), U20.1 (VOUT), U26.1 (VOUT), U32.1 (VOUT)
unnamed: J15.2 (B), J34.2 (B), J53.2 (B), J72.2 (B), J91.2 (B), J110.2 (B), R18.2, R39.2, R60.2, R81.2, R102.2, R123.2, U5.2 (VDD), U11.2 (VDD), U17.2 (VDD), U23.2 (VDD), U29.2 (VDD), U35.2 (VDD)
unnamed: J16.2 (B), J35.2 (B), J54.2 (B), J73.2 (B), J92.2 (B), J111.2 (B), R18.1, R20.2, R39.1, R41.2, R60.1, R62.2, R81.1, R83.2, R102.1, R104.2, R123.1, R125.2, U5.1 (VOUT), U11.1 (VOUT), U17.1 (VOUT), U23.1 (VOUT), U29.1 (VOUT), U35.1 (VOUT)
unnamed: J17.2 (B), J36.2 (B), J55.2 (B), J74.2 (B), J93.2 (B), J112.2 (B), TP4.1, TP9.1, TP14.1, TP19.1, TP24.1, TP29.1, U6.1 (VIN), U12.1 (VIN), U18.1 (VIN), U24.1 (VIN), U30.1 (VIN), U36.1 (VIN)
unnamed: Q1.3 (D), Q2.1 (G), Q7.3 (D), Q9.1 (G), Q21.3 (D), Q22.1 (G), Q31.3 (D), Q32.1 (G), Q41.3 (D), Q42.1 (G), Q51.3 (D), Q52.1 (G), R2.1, R23.1, R44.1, R65.1, R86.1, R107.1, TP1.1, TP6.1, TP11.1, TP16.1, TP21.1, TP26.1
unnamed: Q2.3 (D), Q9.3 (D), Q22.3 (D), Q32.3 (D), Q42.3 (D), Q52.3 (D), R15.2, R36.2, R57.2, R78.2, R99.2, R120.2
unnamed: Q4.3 (D), Q5.1 (G), Q14.3 (D), Q15.1 (G), Q24.3 (D), Q25.1 (G), Q34.3 (D), Q35.1 (G), Q44.3 (D), Q45.1 (G), Q54.3 (D), Q55.1 (G), R8.1, R29.1, R50.1, R71.1, R92.1, R113.1, TP2.1, TP7.1, TP12.1, TP17.1, TP22.1, TP27.1
unnamed: Q6.3 (D), Q8.1 (G), Q16.3 (D), Q17.1 (G), Q26.3 (D), Q27.1 (G), Q36.3 (D), Q37.1 (G), Q46.3 (D), Q47.1 (G), Q56.3 (D), Q57.1 (G), R11.1, R32.1, R53.1, R74.1, R95.1, R116.1, TP3.1, TP8.1, TP13.1, TP18.1, TP23.1, TP28.1
unnamed: C1.1, C4.1, C7.1, C10.1, C13.1, C16.1, Q10.3 (D), Q12.3 (D), Q18.3 (D), Q20.3 (D), Q28.3 (D), Q30.3 (D), Q38.3 (D), Q40.3 (D), Q48.3 (D), Q50.3 (D), Q58.3 (D), Q60.3 (D), U1.3 (VI), U7.3 (VI), U13.3 (VI), U19.3 (VI), U25.3 (VI), U31.3 (VI)
unnamed: Q11.3 (D), Q12.1 (G), Q19.3 (D), Q20.1 (G), Q29.3 (D), Q30.1 (G), Q39.3 (D), Q40.1 (G), Q49.3 (D), Q50.1 (G), Q59.3 (D), Q60.1 (G), R14.1, R35.1, R56.1, R77.1, R98.1, R119.1
unnamed: R4.2, R15.1, R25.2, R36.1, R46.2, R57.1, R67.2, R78.1, R88.2, R99.1, R109.2, R120.1
unnamed: R12.2, R33.2, R54.2, R75.2, R96.2, R117.2, U4.3 (SET), U10.3 (SET), U16.3 (SET), U22.3 (SET), U28.3 (SET), U34.3 (SET)
unnamed: C2.2, C5.2, C8.2, C11.2, C14.2, C17.2, L1.1, L2.1, L3.1, L4.1, L5.1, L6.1, U6.2 (SW), U12.2 (SW), U18.2 (SW), U24.2 (SW), U30.2 (SW), U36.2 (SW)
unnamed: C2.1, C5.1, C8.1, C11.1, C14.1, C17.1, U6.4 (VBST), U12.4 (VBST), U18.4 (VBST), U24.4 (VBST), U30.4 (VBST), U36.4 (VBST)
unnamed: R16.2, R19.2, R37.2, R40.2, R58.2, R61.2, R79.2, R82.2, R100.2, R103.2, R121.2, R124.2, TP5.1, TP10.1, TP15.1, TP20.1, TP25.1, TP30.1, U6.6 (VFB), U12.6 (VFB), U18.6 (VFB), U24.6 (VFB), U30.6 (VFB), U36.6 (VFB)
PWR_SENSORS: J9.5, J28.5, J47.5, J66.5, J85.5, J104.5, Q3.3 (D), Q13.3 (D), Q23.3 (D), Q33.3 (D), Q43.3 (D), Q53.3 (D)
RST: J12.14, J19.6, J19.14, J31.14, J38.6, J38.14, J50.14, J57.6, J57.14, J69.14, J76.6, J76.14, J88.14, J95.6, J95.14, J107.14, J114.6, J114.14
SCK: J12.16, J19.17, J31.16, J38.17, J50.16, J57.17, J69.16, J76.17, J88.16, J95.17, J107.16, J114.17
SOLAR/IN+: J7.2, J26.2, J45.2, J64.2, J83.2, J102.2
SW_CHARGER: J9.2, J16.1 (A), J28.2, J35.1 (A), J47.2, J54.1 (A), J66.2, J73.1 (A), J85.2, J92.1 (A), J104.2, J111.1 (A), Q4.1 (G), Q14.1 (G), Q24.1 (G), Q34.1 (G), Q44.1 (G), Q54.1 (G), R7.2, R28.2, R49.2, R70.2, R91.2, R112.2, U6.5 (EN), U12.5 (EN), U18.5 (EN), U24.5 (EN), U30.5 (EN), U36.5 (EN)
SW_DIVIDER: J9.3, J28.3, J47.3, J66.3, J85.3, J104.3, Q1.1 (G), Q7.1 (G), Q21.1 (G), Q31.1 (G), Q41.1 (G), Q51.1 (G), R1.2, R22.2, R43.2, R64.2, R85.2, R106.2
SW_PWR1: J9.8, J14.1 (A), J28.8, J33.1 (A), J47.8, J52.1 (A), J66.8, J71.1 (A), J85.8, J90.1 (A), J104.8, J109.1 (A), Q6.1 (G), Q16.1 (G), Q26.1 (G), Q36.1 (G), Q46.1 (G), Q56.1 (G), R9.2, R30.2, R51.2, R72.2, R93.2, R114.2
SW_PWR2: J9.9, J13.1 (A), J28.9, J32.1 (A), J47.9, J51.1 (A), J66.9, J70.1 (A), J85.9, J89.1 (A), J104.9, J108.1 (A), R10.2, R17.2, R31.2, R38.2, R52.2, R59.2, R73.2, R80.2, R94.2, R101.2, R115.2, R122.2, U3.2 (A), U4.4 (ON), U9.2 (A), U10.4 (ON), U15.2 (A), U16.4 (ON), U21.2 (A), U22.4 (ON), U27.2 (A), U28.4 (ON), U33.2 (A), U34.4 (ON)
SW_SENSORS: J9.6, J28.6, J47.6, J66.6, J85.6, J104.6, Q3.1 (G), Q13.1 (G), Q23.1 (G), Q33.1 (G), Q43.1 (G), Q53.1 (G), R3.1, R24.1, R45.1, R66.1, R87.1, R108.1
TP4056_PWR: C3.2, C6.2, C9.2, C12.2, C15.2, C18.2, J9.1, J28.1, J47.1, J66.1, J85.1, J104.1, L1.2, L2.2, L3.2, L4.2, L5.2, L6.2, Q5.3 (D), Q15.3 (D), Q25.3 (D), Q35.3 (D), Q45.3 (D), Q55.3 (D), R19.1, R40.1, R61.1, R82.1, R103.1, R124.1
VCC/BATT: J9.12, J28.12, J47.12, J66.12, J85.12, J104.12, Q8.2 (S), Q10.2 (S), Q17.2 (S), Q18.2 (S), Q27.2 (S), Q28.2 (S), Q37.2 (S), Q38.2 (S), Q47.2 (S), Q48.2 (S), Q57.2 (S), Q58.2 (S), R11.2, R32.2, R53.2, R74.2, R95.2, R116.2, U3.1 (B), U3.5 (VCC), U4.5 (IN), U9.1 (B), U9.5 (VCC), U10.5 (IN), U15.1 (B), U15.5 (VCC), U16.5 (IN), U21.1 (B), U21.5 (VCC), U22.5 (IN), U27.1 (B), U27.5 (VCC), U28.5 (IN), U33.1 (B), U33.5 (VCC), U34.5 (IN)
